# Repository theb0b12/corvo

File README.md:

# corvo
This is a cornix inspired ergogen'd pcb.

**This was a commissioned build, but it is open source under the AGPL v3 License**

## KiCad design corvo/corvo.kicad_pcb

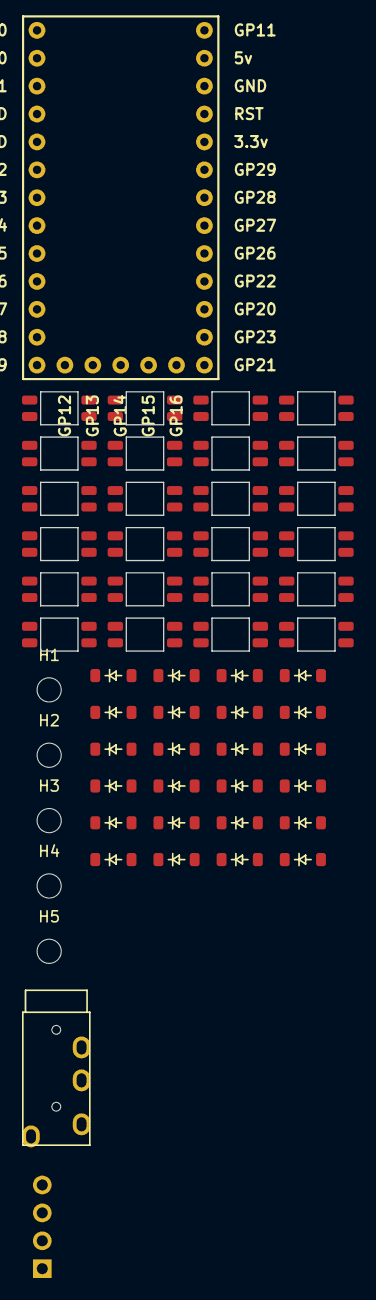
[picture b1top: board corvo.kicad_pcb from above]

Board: 2 copper layers, 80 parts (0 on the bottom side), 24 nets, no tracks yet.

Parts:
D1, D2, D3, D4, D5, D6, D8, D9, D10, D11, D12, D13, D14, D15, D16, D17, D18, D19, D20, D21, D22, D23, D24, D25: LED_SK6812MINI
D7, D26, D27, D28, D29, D30, D31, D32, D33, D34, D35, D36, D37, D38, D39, D40, D41, D42, D43, D44, D45, D46, D47, D48: Diode_SOD-123
H1, H2, H3, H4, H5: MountingHole_2.2mm_M2
J1: OLED_128x32
S1, S2, S3, S4, S5, S6, S7, S8, S9, S10, S11, S12, S13, S14, S15, S16, S17, S18, S19, S20, S21, S22, S23, S24: Hotswap_Choc_V1V2_1.00u
U1: RP2040_Pro_Micro
U2: TRRS; TRRS_PJ-320A

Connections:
unnamed: D7.2 (A_2), S1.2 (2_2)
unnamed: D26.2 (A_2), S2.2 (2_2)
unnamed: D27.2 (A_2), S3.2 (2_2)
unnamed: D28.2 (A_2), S4.2 (2_2)
unnamed: D29.2 (A_2), S5.2 (2_2)
unnamed: D30.2 (A_2), S6.2 (2_2)
unnamed: D31.2 (A_2), S7.2 (2_2)
unnamed: D32.2 (A_2), S8.2 (2_2)
unnamed: D33.2 (A_2), S9.2 (2_2)
unnamed: D34.2 (A_2), S10.2 (2_2)
unnamed: D35.2 (A_2), S11.2 (2_2)
unnamed: D36.2 (A_2), S12.2 (2_2)
unnamed: D37.2 (A_2), S13.2 (2_2)
unnamed: D38.2 (A_2), S14.2 (2_2)
unnamed: D39.2 (A_2), S15.2 (2_2)
unnamed: D40.2 (A_2), S16.2 (2_2)
unnamed: D41.2 (A_2), S17.2 (2_2)
unnamed: D42.2 (A_2), S18.2 (2_2)
unnamed: D43.2 (A_2), S19.2 (2_2)
unnamed: D44.2 (A_2), S20.2 (2_2)
unnamed: D45.2 (A_2), S21.2 (2_2)
unnamed: D46.2 (A_2), S22.2 (2_2)
unnamed: D47.2 (A_2), S23.2 (2_2)
unnamed: D48.2 (A_2), S24.2 (2_2)

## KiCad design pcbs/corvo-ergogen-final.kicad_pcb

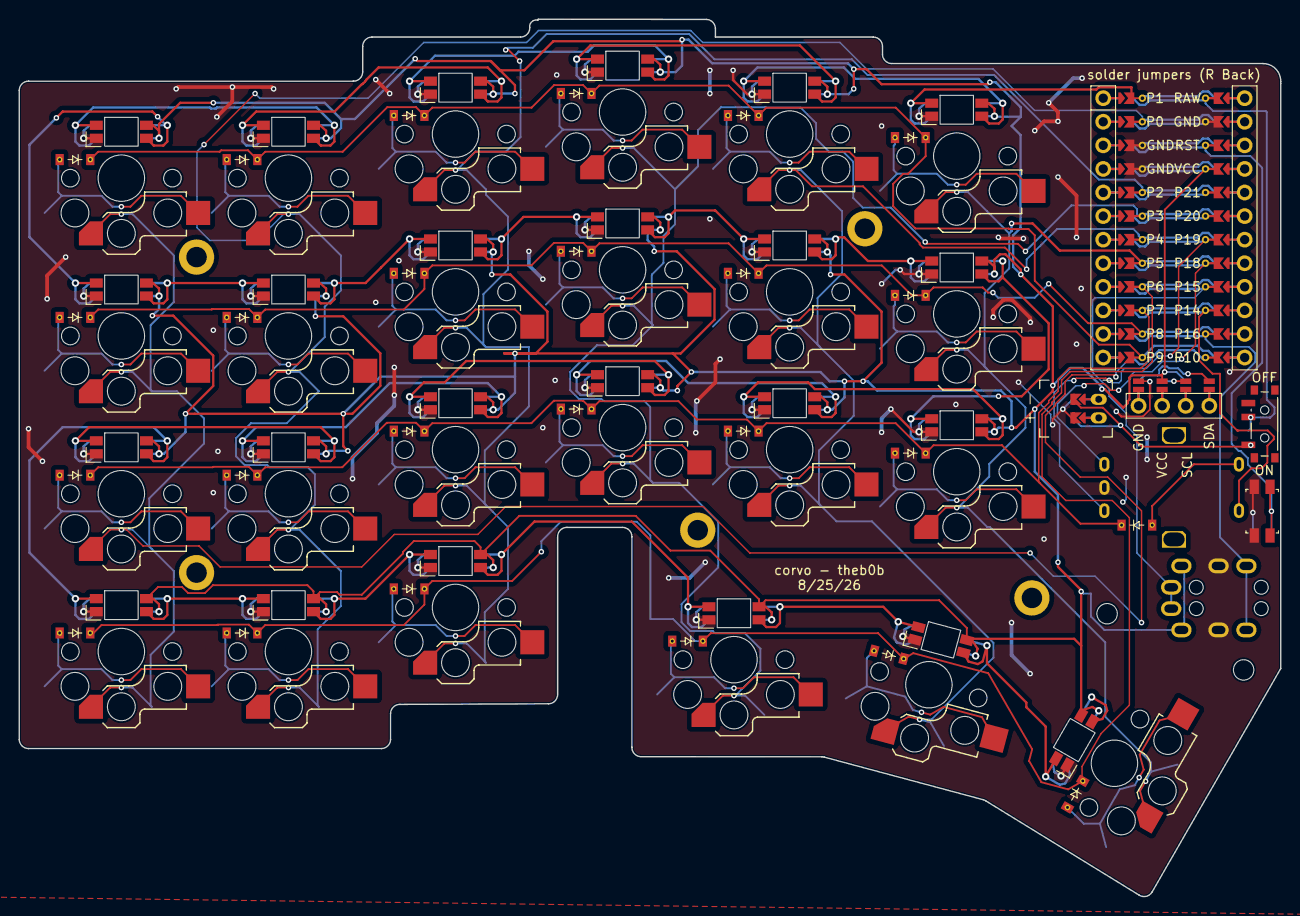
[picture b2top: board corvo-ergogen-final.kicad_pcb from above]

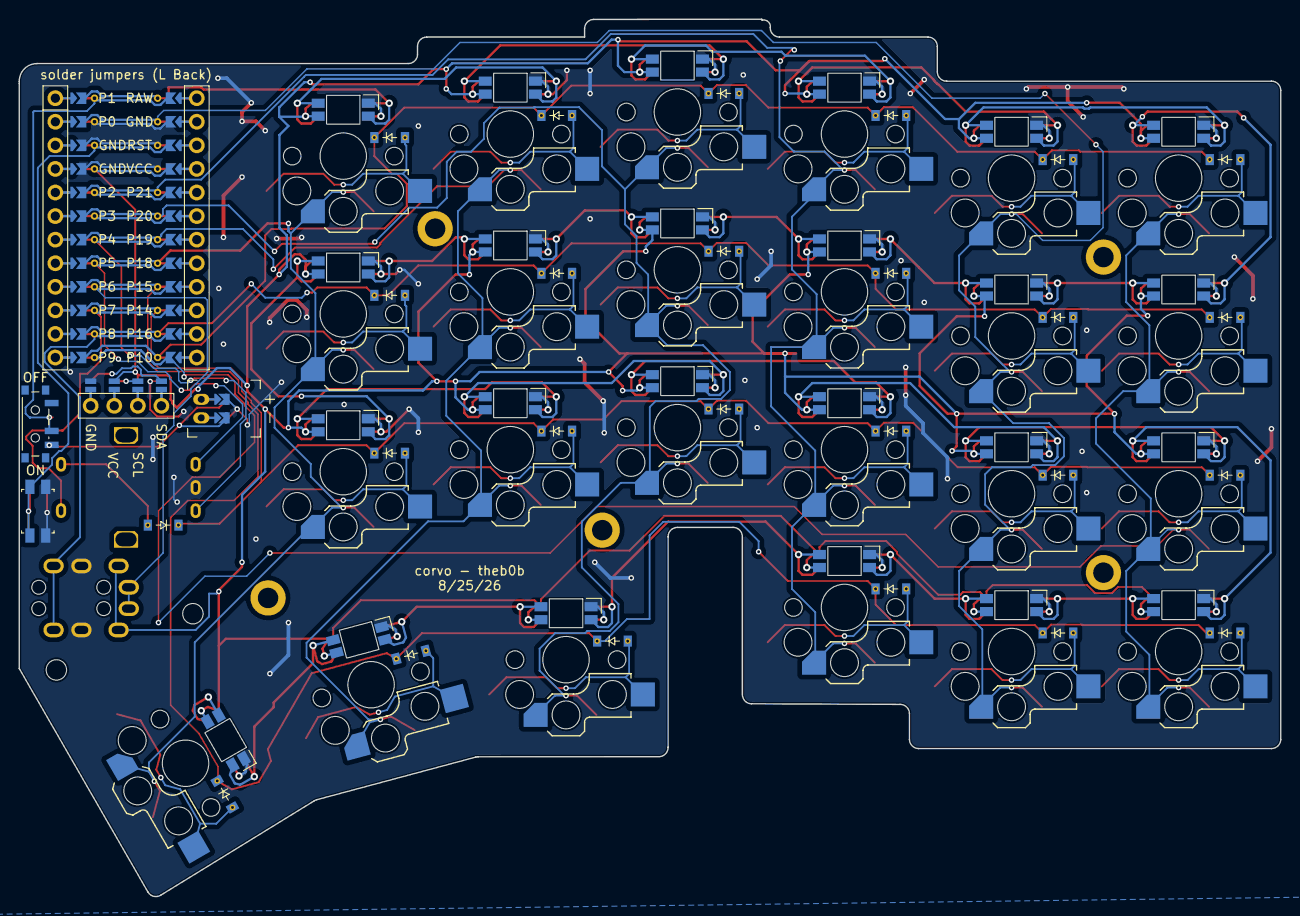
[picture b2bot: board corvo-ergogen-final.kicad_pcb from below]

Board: 2 copper layers, 135.9 x 94.5 mm, 87 parts (48 on the bottom side), 55 nets.

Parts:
D1, D2, D3, D4, D5, D6, D7, D8, D9, D10, D11, D12, D13, D14, D15, D16, D17, D18, D19, D20, D21, D22, D23, D24, D25: ComboDiode
DISP1: display_ssd1306
H1, H2, H3, H4, H5: mounting_hole_plated
JST1: battery_connector_jst_ph_2
LED1, LED2, LED3, LED4, LED5, LED6, LED7, LED8, LED9, LED10, LED11, LED12, LED13, LED14, LED15, LED16, LED17, LED18, LED19, LED20, LED21, LED22, LED23, LED24: led_SK6812mini-e (per-key, reversible)
MCU1: mcu_nice_nano
MH1, MH2: mounting_hole_npth
PWR1: power_switch_smd_side
RE1: rotary_encoder_ec11_ec12
RST1: reset_switch_smd_side
S1, S2, S3, S4, S5, S6, S7, S8, S9, S10, S11, S12, S13, S14, S15, S16, S17, S18, S19, S20, S21, S22, S23, S24: switch_choc_v1_v2
TRRS1: trrs_pj320a (reversible)

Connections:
BAT_P: JST1.1, PWR1.1, PWR1.3
DISP1_1: DISP1.1, DISP1.10, DISP1.23
DISP1_2: DISP1.2, DISP1.11, DISP1.22
DISP1_3: DISP1.3, DISP1.12, DISP1.21
DISP1_4: DISP1.4, DISP1.13, DISP1.20
GND: DISP1.14, DISP1.24, JST1.2, LED1.3, LED2.3, LED3.3, LED4.3, LED5.3, LED6.3, LED7.3, LED8.3, LED9.3, LED10.3, LED11.3, LED12.3, LED13.3, LED14.3, LED15.3, LED16.3, LED17.3, LED18.3, LED19.3, LED20.3, LED21.3, LED22.3, LED23.3, LED24.3, MCU1.102, MCU1.121, MCU1.122, RE1.B, RST1.2, RST1.4, TRRS1.3
JST1_1: JST1.11, JST1.21, JST1.31
JST1_2: JST1.12, JST1.22, JST1.32
P0: MCU1.123, S5.1, S6.1, S7.1, S8.1
P1: LED21.4, MCU1.124
P2: MCU1.120, S9.1, S10.1, S11.1, S12.1
P3: MCU1.119, S13.1, S14.1, S15.1, S22.1
P4: MCU1.118, S16.1, S17.1, S18.1, S23.1
P5: MCU1.117, S19.1, S20.1, S21.1, S24.1
P6: D1.1, D5.1, D9.1, D22.1, D23.1, D24.1, MCU1.116
P7: D2.1, D6.1, D10.1, D13.1, D16.1, D19.1, D25.1, MCU1.115
P8: D3.1, D7.1, D11.1, D14.1, D17.1, D20.1, MCU1.114
P9: D4.1, D8.1, D12.1, D15.1, D18.1, D21.1, MCU1.113
P10: MCU1.112, S1.1, S2.1, S3.1, S4.1
P14: MCU1.110, RE1.S2
P15: MCU1.109, TRRS1.5
P16: MCU1.111, TRRS1.2
P18: MCU1.108, RE1.C
P19: MCU1.107, RE1.A
RAW: MCU1.101, PWR1.2
RST: MCU1.103, RST1.1, RST1.3
SCL: DISP1.16, DISP1.26
SDA: DISP1.17, DISP1.27
VCC: DISP1.15, DISP1.25, LED1.1, LED2.1, LED3.1, LED4.1, LED5.1, LED6.1, LED7.1, LED8.1, LED9.1, LED10.1, LED11.1, LED12.1, LED13.1, LED14.1, LED15.1, LED16.1, LED17.1, LED18.1, LED19.1, LED20.1, LED21.1, LED22.1, LED23.1, LED24.1, MCU1.104, TRRS1.4
c1_r1: D4.1, D4.2, S4.2
c1_r2: D3.1, D3.2, S3.2
c1_r3: D2.1, D2.2, S2.2
c1_r4: D1.1, D1.2, S1.2
c2_r1: D8.1, D8.2, S8.2
c2_r2: D7.1, D7.2, S7.2
c2_r3: D6.1, D6.2, S6.2
c2_r4: D5.1, D5.2, S5.2
c3_r1: D12.1, D12.2, S12.2
c3_r2: D11.1, D11.2, S11.2
c3_r3: D10.1, D10.2, S10.2
c3_r4: D9.1, D9.2, S9.2
c4_r0: D22.1, D22.2, S22.2
c4_r1: D15.1, D15.2, S15.2
c4_r2: D14.1, D14.2, S14.2
c4_r3: D13.1, D13.2, S13.2
c5_r0: D23.1, D23.2, S23.2
c5_r1: D18.1, D18.2, S18.2
c5_r2: D17.1, D17.2, S17.2
c5_r3: D16.1, D16.2, S16.2
c6_r0: D24.1, D24.2, S24.2
c6_r1: D21.1, D21.2, S21.2
c6_r2: D20.1, D20.2, S20.2
c6_r3: D19.1, D19.2, S19.2
encoder: D25.1, D25.2, RE1.S1
rgb: LED1.2, LED1.4, LED2.2, LED2.4, LED3.2, LED3.4, LED4.2, LED4.4, LED5.2, LED5.4, LED6.2, LED6.4, LED7.2, LED7.4, LED8.2, LED8.4, LED9.2, LED9.4, LED10.2, LED10.4, LED11.2, LED11.4, LED12.2, LED12.4, LED13.2, LED13.4, LED14.2, LED14.4, LED15.2, LED15.4, LED16.2, LED16.4, LED17.2, LED17.4, LED18.2, LED18.4, LED19.2, LED19.4, LED20.2, LED20.4, LED21.2, LED22.2, LED22.4, LED23.2, LED23.4, LED24.2, LED24.4
